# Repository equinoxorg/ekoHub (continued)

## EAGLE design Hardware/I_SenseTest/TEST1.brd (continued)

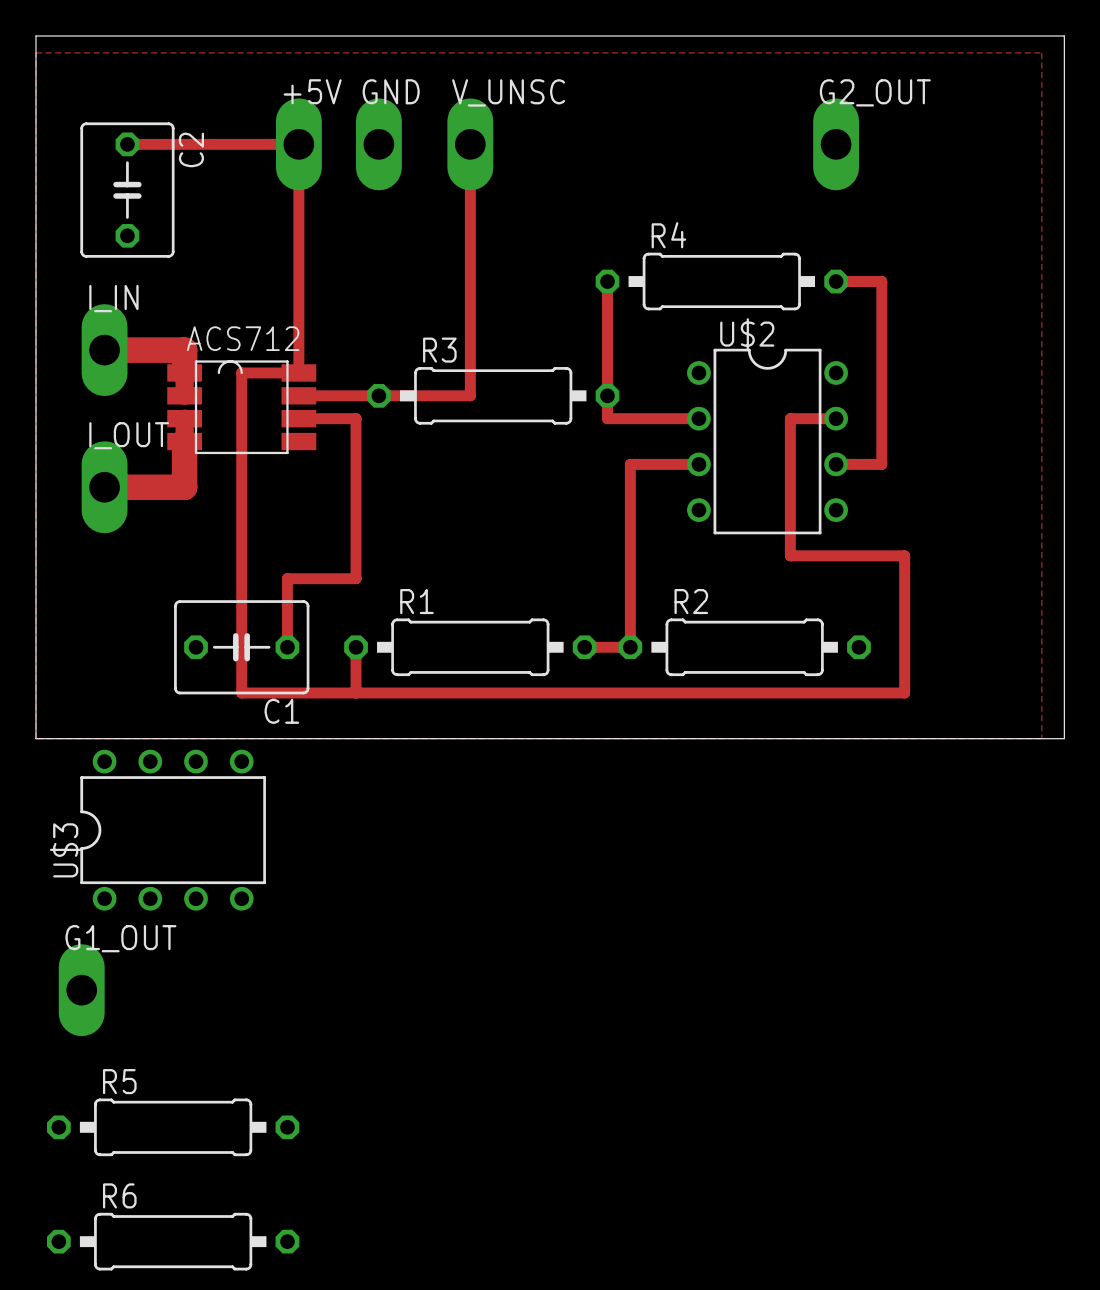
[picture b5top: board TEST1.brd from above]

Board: 2 copper layers, 57.1 x 39.0 mm, 18 parts (0 on the bottom side), 11 nets.

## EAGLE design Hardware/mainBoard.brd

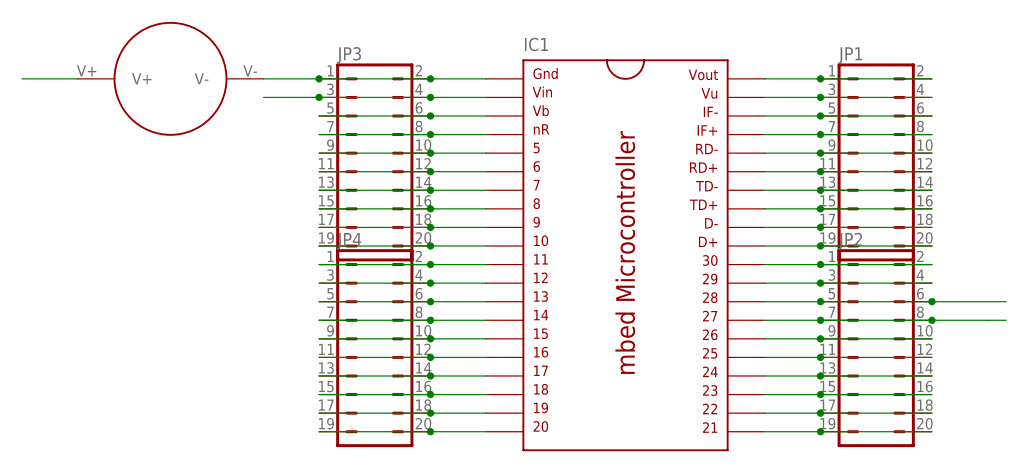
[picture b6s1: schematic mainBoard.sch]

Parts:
IC1: MBED_MICROCONTROLLER; DIL40_0.9
JP1, JP2, JP3, JP4: JP10Q
U$1: PANASONIC_BATTERYTHROUGH_HOLE; PANASONIC_BATTERY

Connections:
unnamed: IC1.1, JP3.1, JP3.2, U$1.V-
unnamed: IC1.40, JP1.1, JP1.2
unnamed: IC1.39, JP1.3, JP1.4
unnamed: IC1.38, JP1.5, JP1.6
unnamed: IC1.37, JP1.7, JP1.8
unnamed: IC1.36, JP1.9, JP1.10
unnamed: IC1.35, JP1.11, JP1.12
unnamed: IC1.34, JP1.13, JP1.14
unnamed: IC1.33, JP1.15, JP1.16
unnamed: IC1.32, JP1.17, JP1.18
unnamed: IC1.31, JP1.19, JP1.20
unnamed: IC1.30, JP2.1, JP2.2
unnamed: IC1.29, JP2.3, JP2.4
unnamed: IC1.26, JP2.9, JP2.10
unnamed: IC1.25, JP2.11, JP2.12
unnamed: IC1.24, JP2.13, JP2.14
unnamed: IC1.23, JP2.15, JP2.16
unnamed: IC1.22, JP2.17, JP2.18
unnamed: IC1.21, JP2.19, JP2.20
unnamed: IC1.4, JP3.7, JP3.8
unnamed: IC1.5, JP3.9, JP3.10
unnamed: IC1.6, JP3.11, JP3.12
unnamed: IC1.7, JP3.13, JP3.14
unnamed: IC1.8, JP3.15, JP3.16
unnamed: IC1.9, JP3.17, JP3.18
unnamed: IC1.10, JP3.19, JP3.20
unnamed: IC1.11, JP4.1, JP4.2
unnamed: IC1.12, JP4.3, JP4.4
unnamed: IC1.13, JP4.5, JP4.6
unnamed: IC1.14, JP4.7, JP4.8
unnamed: IC1.15, JP4.9, JP4.10
unnamed: IC1.16, JP4.11, JP4.12
unnamed: IC1.17, JP4.13, JP4.14
unnamed: IC1.18, JP4.15, JP4.16
unnamed: IC1.19, JP4.17, JP4.18
unnamed: IC1.20, JP4.19, JP4.20
SCL: IC1.27, JP2.7, JP2.8
SDA: IC1.28, JP2.5, JP2.6
VB: IC1.3, JP3.5, JP3.6, U$1.V+
VIN: IC1.2, JP3.3, JP3.4

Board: 2 copper layers, 6 parts (0 on the bottom side), 40 nets, no tracks yet.

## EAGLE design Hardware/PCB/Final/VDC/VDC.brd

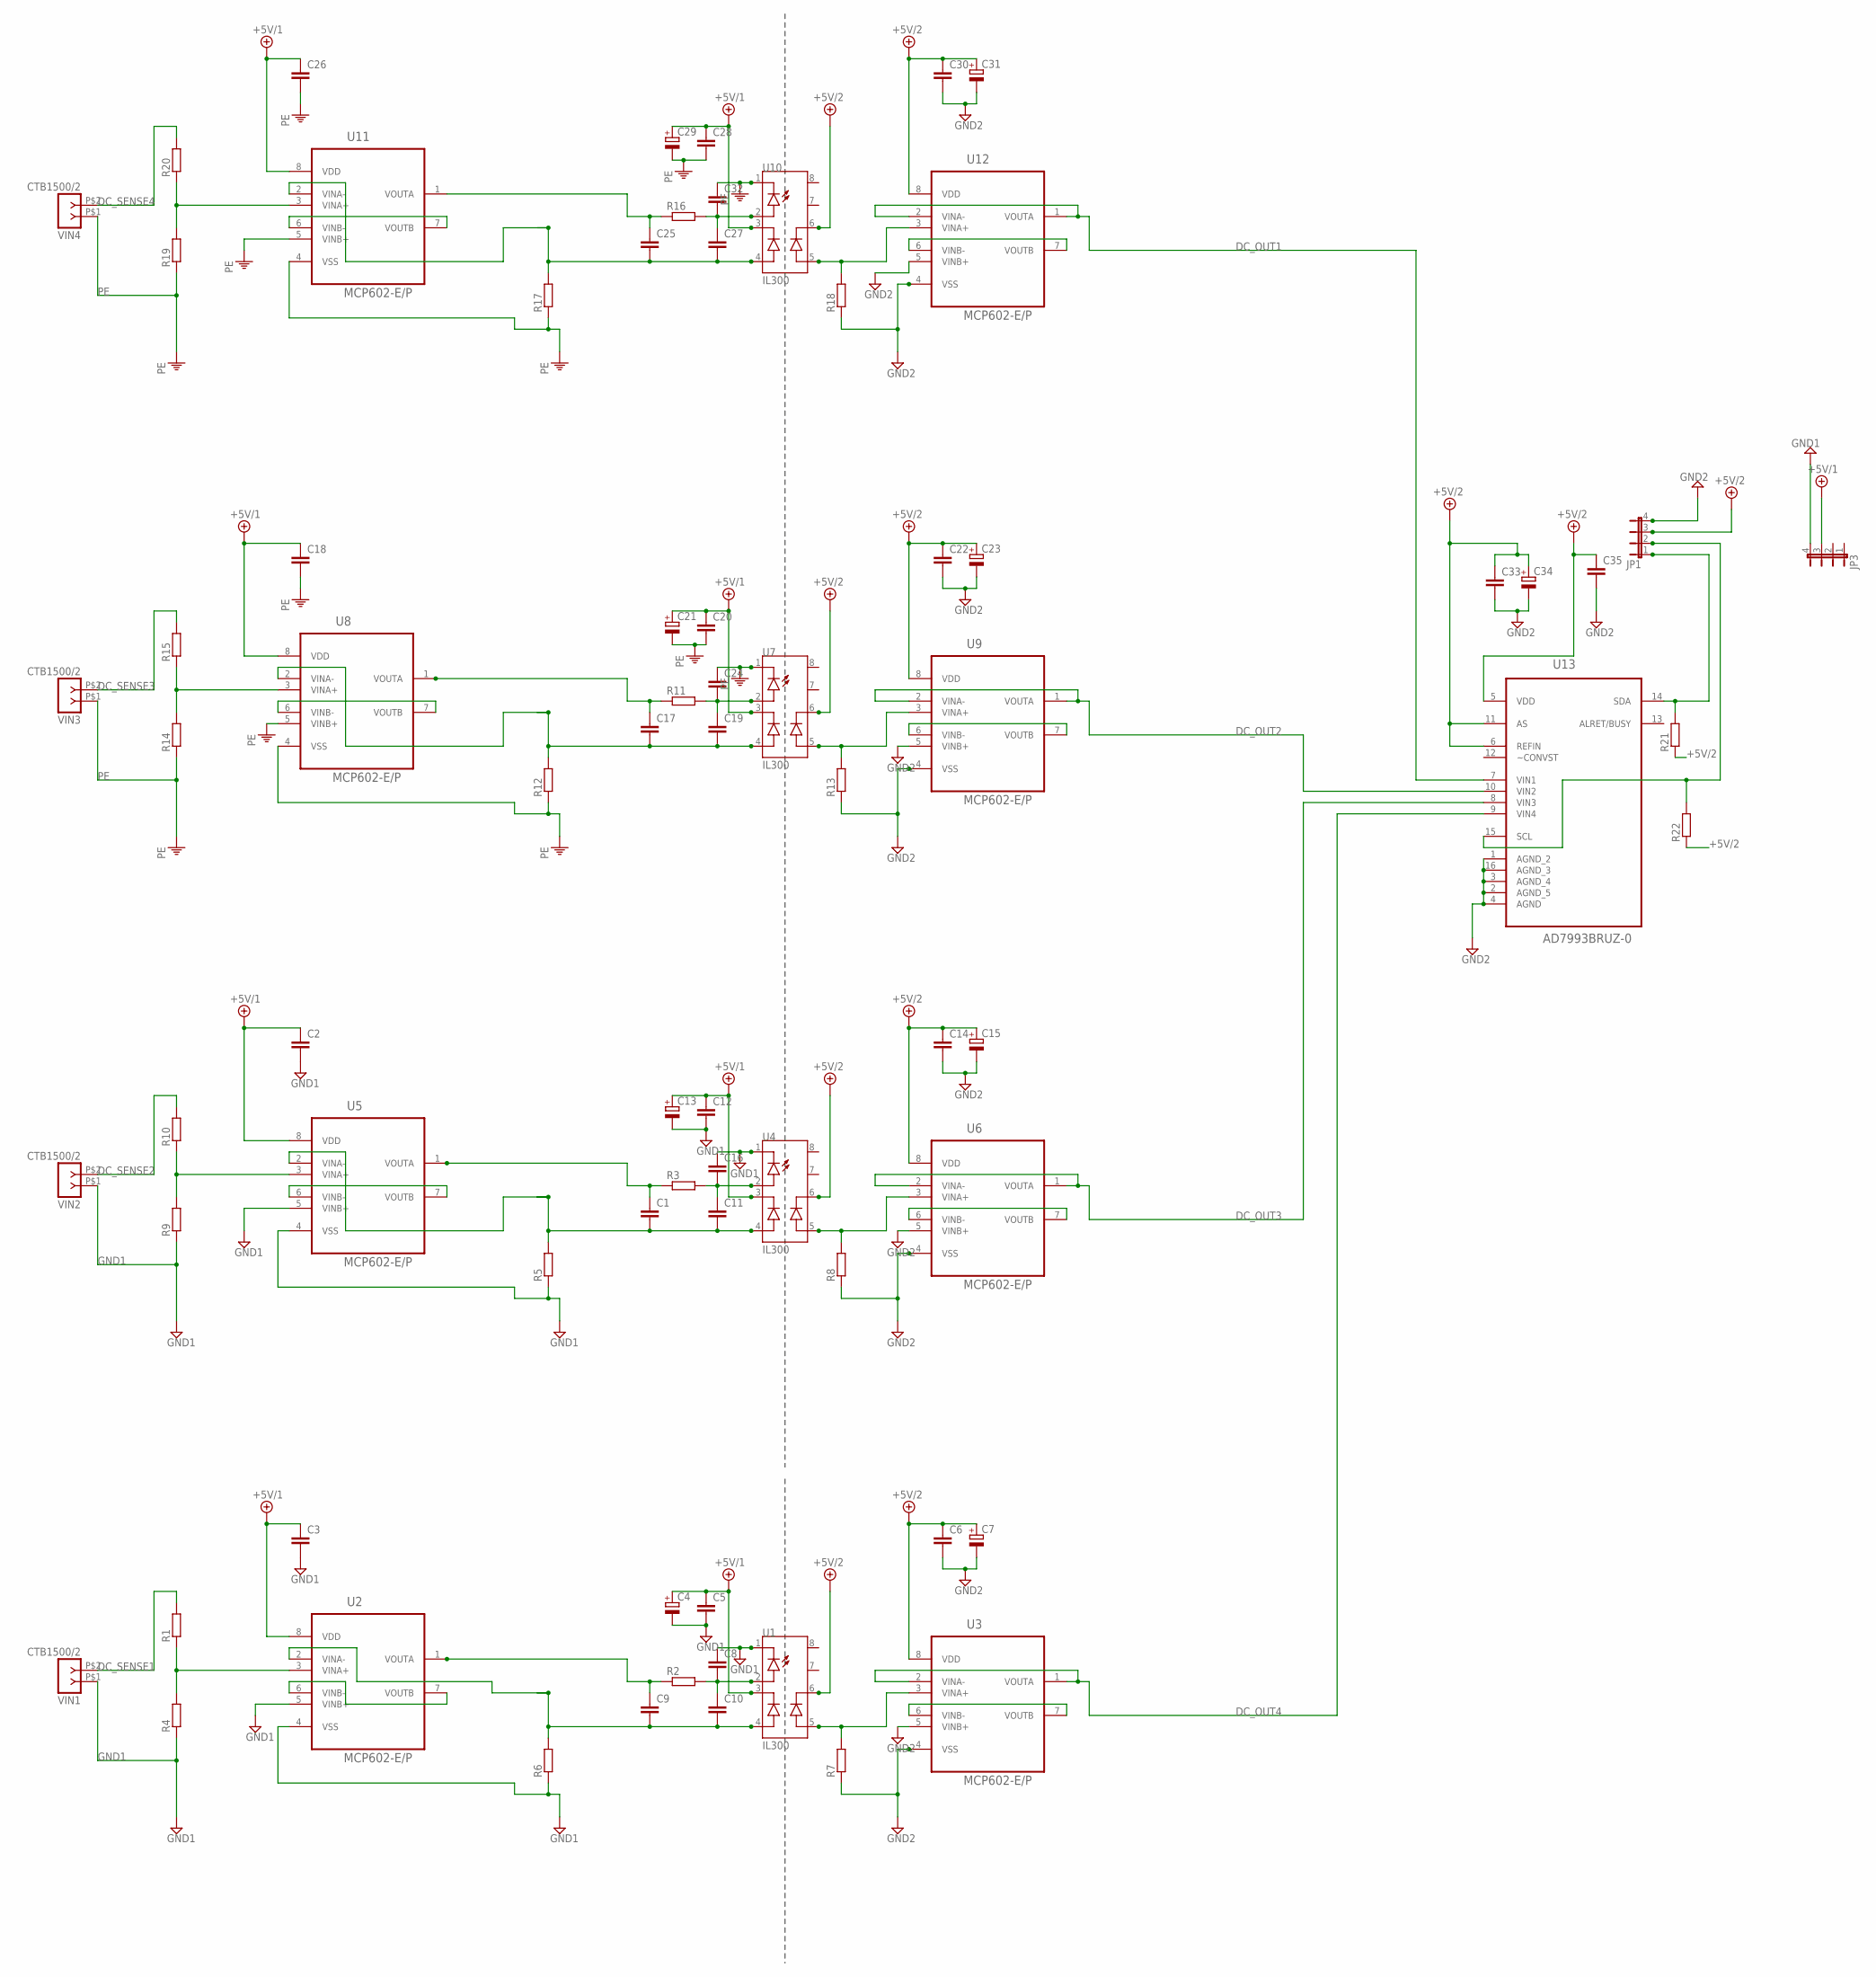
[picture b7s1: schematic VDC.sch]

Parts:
C1, C2, C3, C5, C6, C8, C9, C10, C11, C12, C14, C16, C17, C18, C19, C20, C22, C24, C25, C26, C27, C28, C30, C32: C-EU025-040X050; C025-040X050
C4, C7, C13, C15, C21, C23, C29, C31: CPOL-EUE2-5; E2-5
C33: C-EU025-024X044; C025-024X044
C34: CPOL-EUE2-4; E2-4
C35: C-EU025-025X050; C025-025X050
JP1, JP3: JP4E; JP4
R1, R2, R3, R4, R5, R6, R7, R8, R9, R10, R11, R12, R13, R14, R15, R16, R17, R18, R19, R20, R21, R22: R-EU_0207/10; 0207/10
U1, U4, U7, U10: IL300; DIL08
U2, U3, U5, U6, U8, U9, U11, U12: MCP602-E/P; DIP254P762X508-8P
U13: AD7993BRUZ-0; SOP65P640X120-16N
VIN1, VIN2, VIN3, VIN4: CTB1500/2; CTB1500-2

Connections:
+5V/1: C2.1, C3.1, C4.+, C5.1, C12.1, C13.+, C18.1, C20.1, C21.+, C26.1, C28.1, C29.+, JP3.3, U1.3 (C_FB), U2.8 (VDD), U4.3 (C_FB), U5.8 (VDD), U7.3 (C_FB), U8.8 (VDD), U10.3 (C_FB), U11.8 (VDD)
+5V/2: C6.1, C7.+, C14.1, C15.+, C22.1, C23.+, C30.1, C31.+, C33.1, C34.+, C35.1, JP1.3, R21.1, R22.1, U1.6 (C_OUT), U3.8 (VDD), U4.6 (C_OUT), U6.8 (VDD), U7.6 (C_OUT), U9.8 (VDD), U10.6 (C_OUT), U12.8 (VDD), U13.5 (VDD), U13.6 (REFIN), U13.11 (AS)
DC_OUT1: U12.1 (VOUTA), U12.2 (VINA-), U13.7 (VIN1)
DC_OUT2: U9.1 (VOUTA), U9.2 (VINA-), U13.10 (VIN2)
DC_OUT3: U6.1 (VOUTA), U6.2 (VINA-), U13.8 (VIN3)
DC_OUT4: U3.1 (VOUTA), U3.2 (VINA-), U13.9 (VIN4)
DC_SENSE1: R1.2, VIN1.P$2 (2)
DC_SENSE2: R10.2, VIN2.P$2 (2)
DC_SENSE3: R15.2, VIN3.P$2 (2)
DC_SENSE4: R20.2, VIN4.P$2 (2)
GND1: C2.2, C3.2, C4.-, C5.2, C8.1, C12.2, C13.-, C16.1, JP3.4, R4.1, R5.1, R6.1, R9.1, U1.1 (C_LED), U2.4 (VSS), U2.5 (VINB+), U4.1 (C_LED), U5.4 (VSS), U5.5 (VINB+), VIN1.P$1 (1), VIN2.P$1 (1)
GND2: C6.2, C7.-, C14.2, C15.-, C22.2, C23.-, C30.2, C31.-, C33.2, C34.-, C35.2, JP1.4, R7.1, R8.1, R13.1, R18.1, U3.4 (VSS), U3.5 (VINB+), U6.4 (VSS), U6.5 (VINB+), U9.4 (VSS), U9.5 (VINB+), U12.4 (VSS), U12.5 (VINB+), U13.1 (AGND_2), U13.2 (AGND_5), U13.3 (AGND_4), U13.4 (AGND), U13.16 (AGND_3)
unnamed: C9.2, C10.2, R6.2, U1.4 (A_FB), U2.2 (VINA-)
unnamed: C1.2, C11.2, R5.2, U4.4 (A_FB), U5.2 (VINA-)
unnamed: R7.2, U1.5 (A_OUT), U3.3 (VINA+)
unnamed: C8.2, C10.1, R2.2, U1.2 (A_LED)
unnamed: C9.1, R2.1, U2.1 (VOUTA)
unnamed: C11.1, C16.2, R3.2, U4.2 (A_LED)
unnamed: C1.1, R3.1, U5.1 (VOUTA)
unnamed: R1.1, R4.2, U2.3 (VINA+)
unnamed: R8.2, U4.5 (A_OUT), U6.3 (VINA+)
unnamed: R9.2, R10.1, U5.3 (VINA+)
unnamed: C17.2, C19.2, R12.2, U7.4 (A_FB), U8.2 (VINA-)
unnamed: C19.1, C24.2, R11.2, U7.2 (A_LED)
unnamed: C17.1, R11.1, U8.1 (VOUTA)
unnamed: R13.2, U7.5 (A_OUT), U9.3 (VINA+)
unnamed: R14.2, R15.1, U8.3 (VINA+)
unnamed: C25.2, C27.2, R17.2, U10.4 (A_FB), U11.2 (VINA-)
unnamed: C27.1, C32.2, R16.2, U10.2 (A_LED)
unnamed: C25.1, R16.1, U11.1 (VOUTA)
unnamed: R18.2, U10.5 (A_OUT), U12.3 (VINA+)
unnamed: R19.2, R20.1, U11.3 (VINA+)
unnamed: JP1.1, R21.2, U13.14 (SDA)
unnamed: JP1.2, R22.2, U13.15 (SCL)
unnamed: U11.6 (VINB-), U11.7 (VOUTB)
unnamed: U12.6 (VINB-), U12.7 (VOUTB)
unnamed: U8.6 (VINB-), U8.7 (VOUTB)
unnamed: U9.6 (VINB-), U9.7 (VOUTB)
unnamed: U5.6 (VINB-), U5.7 (VOUTB)
unnamed: U6.6 (VINB-), U6.7 (VOUTB)
unnamed: U2.6 (VINB-), U2.7 (VOUTB)
unnamed: U3.6 (VINB-), U3.7 (VOUTB)
PE: C18.2, C20.2, C21.-, C24.1, C26.2, C28.2, C29.-, C32.1, R12.1, R14.1, R17.1, R19.1, U7.1 (C_LED), U8.4 (VSS), U8.5 (VINB+), U10.1 (C_LED), U11.4 (VSS), U11.5 (VINB+), VIN3.P$1 (1), VIN4.P$1 (1)

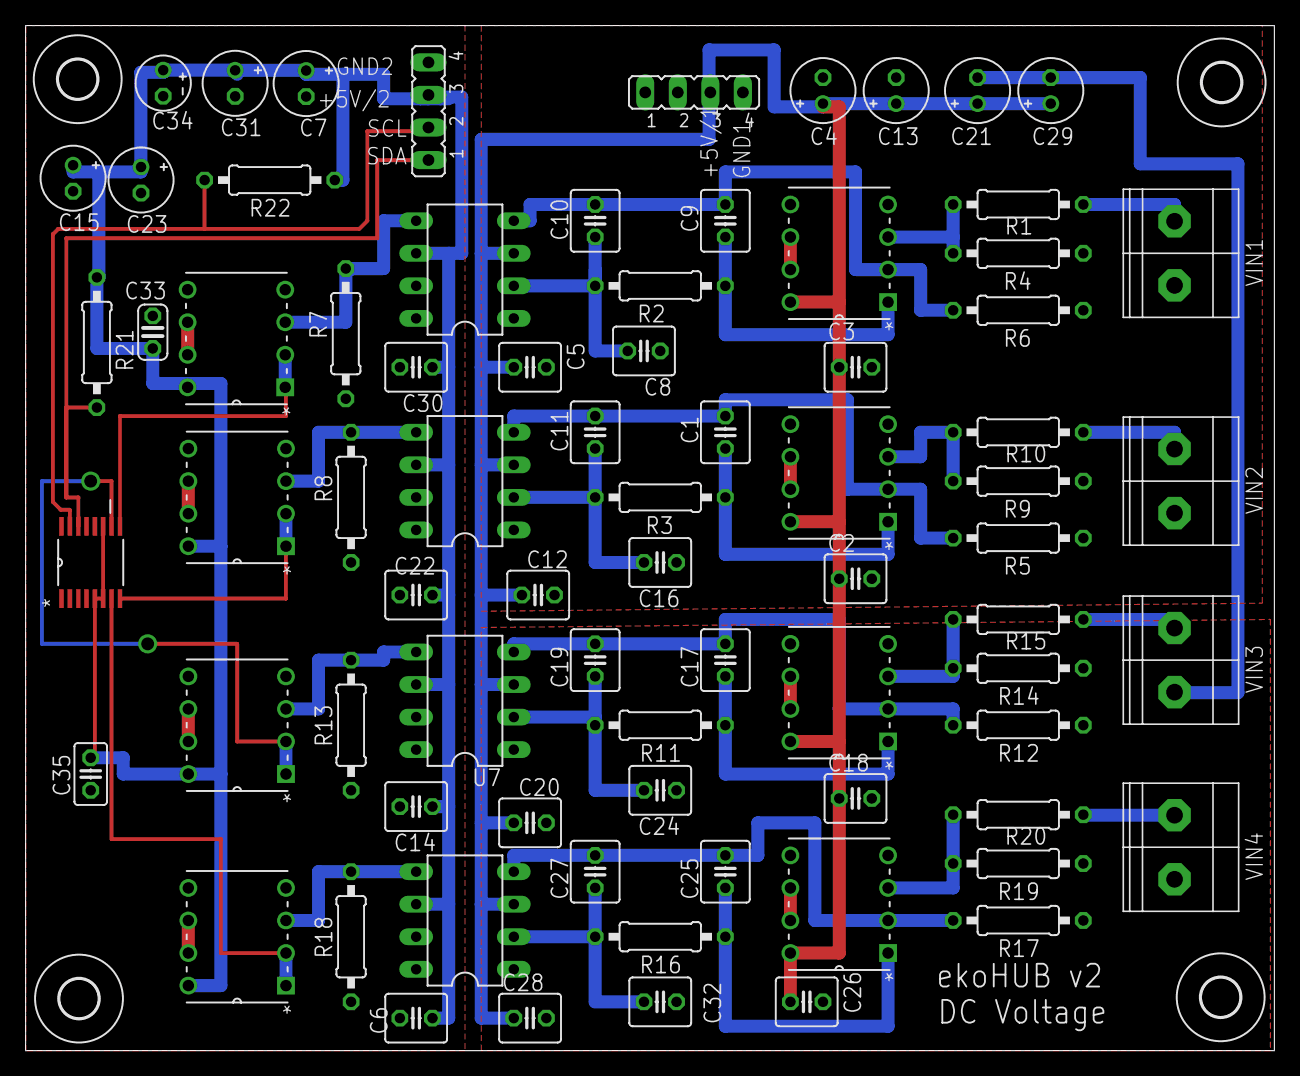
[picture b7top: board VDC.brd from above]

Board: 2 copper layers, 97.5 x 80.0 mm, 80 parts (0 on the bottom side), 43 nets.

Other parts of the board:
U$1, U$2, U$3, U$4: 3,0

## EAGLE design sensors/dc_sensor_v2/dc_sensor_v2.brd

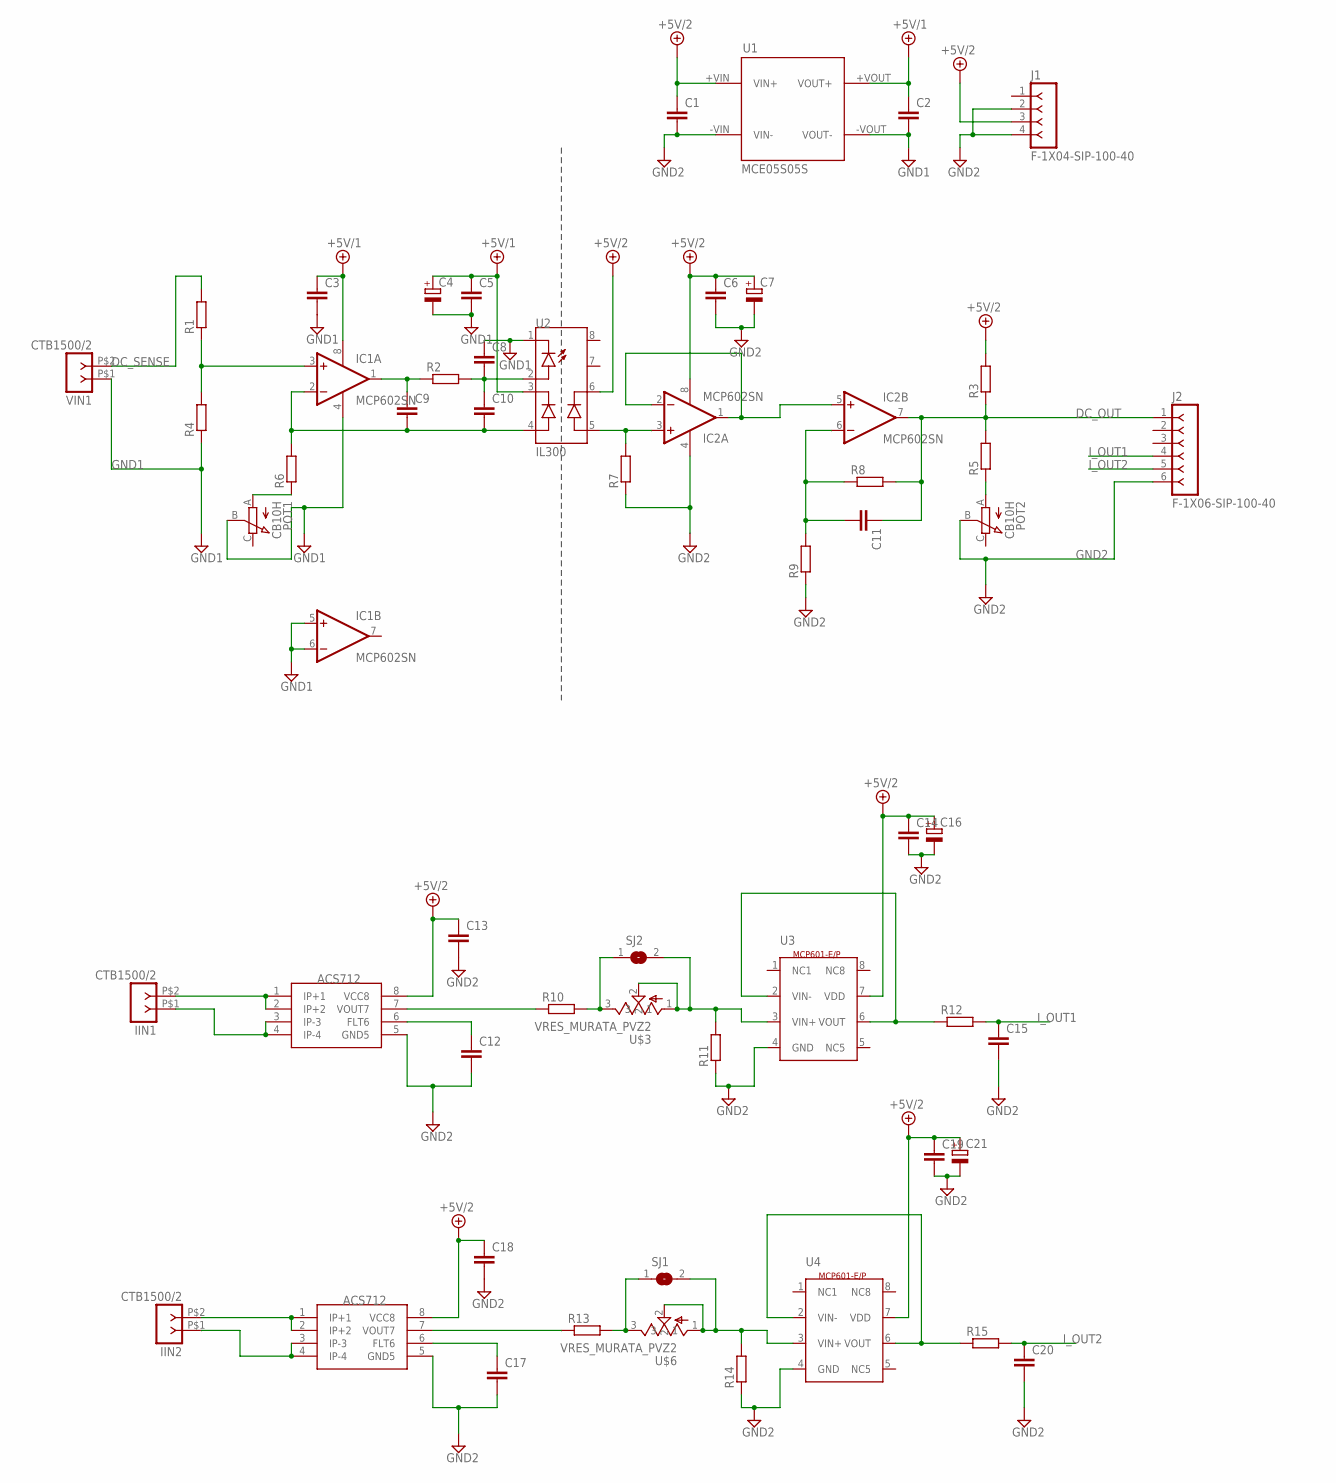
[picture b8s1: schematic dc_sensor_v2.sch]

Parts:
C1, C2: C-EUC1206; C1206
C3, C5, C6, C8, C9, C10, C11: C-EU025-040X050; C025-040X050
C4, C7: CPOL-EUE2-5; E2-5
C12, C15, C17, C20: C-EU025-030X050; C025-030X050
C13, C14, C18, C19: C-EUC0603; C0603
C16, C21: CPOL-EUE2.5-6; E2,5-6
IC1, IC2: MCP602SN; SO08
IIN1, IIN2: CTB1500/2; CTB1500-2
J1: F-1X04-SIP-100-40; SIP-100-04-40
J2: F-1X06-SIP-100-40; SIP-100-06-40
POT1, POT2: CB10H; CB10V
R1, R2, R3, R4, R5, R6, R7, R8, R9, R10, R11, R12, R13, R14, R15: R-EU_0207/10; 0207/10
SJ1, SJ2: SJ
U1: MCE05S05S; MCEXXSXXS_SIP
U2: IL300; DIL08
U3, U4: MCP601; SO8
U5, U6: ACS712; SO8
U$3, U$6: VRES_MURATA_PVZ2; MURATA_PVZ2A
VIN1: CTB1500/2; CTB1500-2

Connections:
+5V/1: C2.1, C3.1, C4.+, C5.1, IC1.8 (V+), U1.+VOUT (VOUT+), U2.3 (C_FB)
+5V/2: C1.1, C6.1, C7.+, C13.1, C14.1, C16.+, C18.1, C19.1, C21.+, IC2.8 (V+), J1.3, R3.2, U1.+VIN (VIN+), U2.6 (C_OUT), U3.7 (VDD), U4.7 (VDD), U5.8 (VCC8), U6.8 (VCC8)
DC_OUT: C11.1, IC2.7 (OUT), J2.1, R3.1, R5.2, R8.2
DC_SENSE: R1.2, VIN1.P$2 (2)
GND1: C2.2, C3.2, C4.-, C5.2, C8.1, IC1.4 (V-), IC1.5 (+IN), IC1.6 (-IN), POT1.B (S), R4.1, U1.-VOUT (VOUT-), U2.1 (C_LED), VIN1.P$1 (1)
GND2: C1.2, C6.2, C7.-, C12.2, C13.2, C14.2, C15.2, C16.-, C17.2, C18.2, C19.2, C20.2, C21.-, IC2.4 (V-), J1.2, J1.4, J2.6, POT2.B (S), R7.1, R9.1, R11.1, R14.1, U1.-VIN (VIN-), U3.4 (GND), U4.4 (GND), U5.5 (GND5), U6.5 (GND5)
I_OUT1: C15.1, J2.4, R12.2
I_OUT2: C20.1, J2.5, R15.2
unnamed: C9.2, C10.2, IC1.2 (-IN), R6.2, U2.4 (A_FB)
unnamed: POT2.A, R5.1
unnamed: IC2.3 (+IN), R7.2, U2.5 (A_OUT)
unnamed: C8.2, C10.1, R2.2, U2.2 (A_LED)
unnamed: C9.1, IC1.1 (OUT), R2.1
unnamed: IC2.1 (OUT), IC2.2 (-IN), IC2.5 (+IN)
unnamed: POT1.A, R6.1
unnamed: IC1.3 (+IN), R1.1, R4.2
unnamed: IIN1.P$2 (2), U6.1 (IP+1), U6.2 (IP+2)
unnamed: C11.2, IC2.6 (-IN), R8.1, R9.2
unnamed: IIN1.P$1 (1), U6.3 (IP-3), U6.4 (IP-4)
unnamed: R10.2, SJ2.1, U$3.3
unnamed: C12.1, U6.6 (FLT6)
unnamed: R12.1, U3.2 (VIN-), U3.6 (VOUT)
unnamed: IIN2.P$2 (2), U5.1 (IP+1), U5.2 (IP+2)
unnamed: R10.1, U6.7 (VOUT7)
unnamed: R11.2, SJ2.2, U3.3 (VIN+), U$3.1, U$3.2
unnamed: IIN2.P$1 (1), U5.3 (IP-3), U5.4 (IP-4)
unnamed: C17.1, U5.6 (FLT6)
unnamed: R13.1, U5.7 (VOUT7)
unnamed: R14.2, SJ1.2, U4.3 (VIN+), U$6.1, U$6.2
unnamed: R13.2, SJ1.1, U$6.3
unnamed: R15.1, U4.2 (VIN-), U4.6 (VOUT)

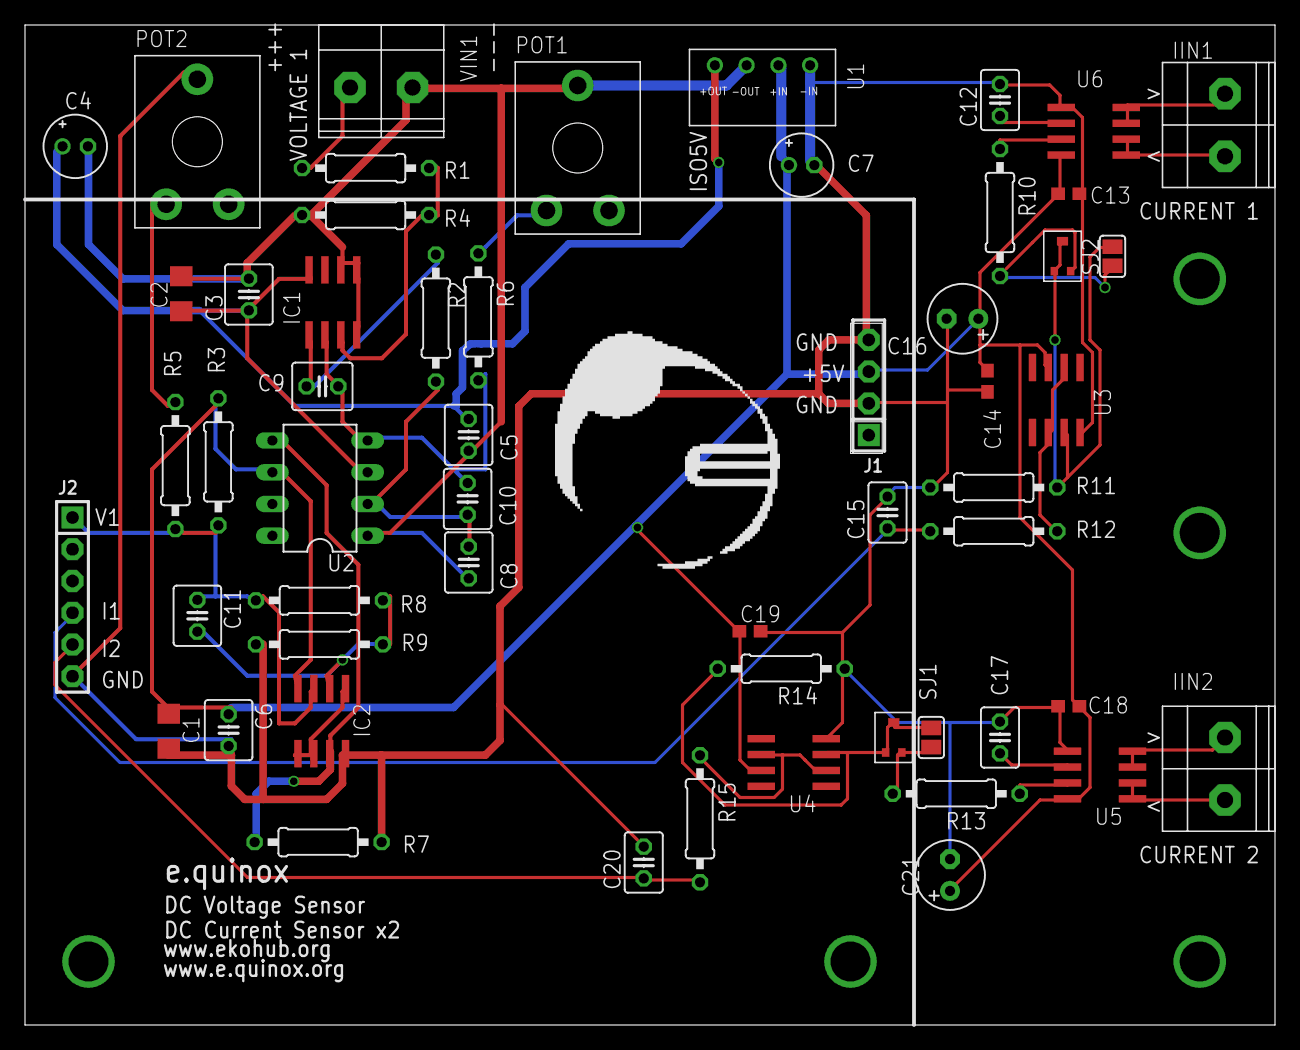
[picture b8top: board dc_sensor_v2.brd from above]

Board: 2 copper layers, 100.0 x 80.0 mm, 56 parts (0 on the bottom side), 31 nets.

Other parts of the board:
U$1: EQNXLOGO

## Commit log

2011-09-18 Initial commit of eko_upload
2011-09-19 Added JSON RPC and CURD interfaces for Messages and Heartbeat
2011-09-19 FileUpload handler added with test code.\nTweaks added to make it play nice with python 2.5 on GAE servers
2011-09-19 Added FileUpoad handler for uploads to blobstore. Fixes for date-time JSON serialisation in Python2.5. Minor cosmetic changes to CSS stylesheets.
2011-09-19 Updated RPCHandlers to make use of memcache when fetching kiosk object and public keys. Removed per function instantiation of BaseConverter(). Added Kiosk Message RPC through function post_message().
2011-09-20 Changes to cache behaviour and templates.
    More handlers now cache data in memcache.
    Data Tables use JQuery ThemeRoller.
    Improvements to layout.
2011-09-25 Minor fixes.
2011-09-25 Fix omission of kiosk id to sync session records.
2011-10-10 Major refactoring. Production Ready.
2011-11-07 Merged some presentation code from legacy project.
2012-02-08 Added cosmetic improvements.
2012-07-23 clean up folder structure
2012-07-23 clean up folder structure 2
    * Removed gerber files, PDFs and other outdated material
    * Reorganised LBR files to library folder
    * Organised board designs into three main categories
2012-07-24 Added FTDI based isolated RS485 test device
    * New footprint for Pheonix Contact PTSM 4-way socket
    * Footrpints for MOLEX 47346-0001, TE1981584-1 and MC32594 USB sockets
    (Micro B, Micro AB and Stacked A respectively).
    * New schematic for FT232R based RS485 adaptor utilising HCPL2630-series
    opto-isolators.
    * Utilised Cliff Electronics 2.1mm SMT DC jack connector from
2012-07-24 Created ftdi_modbus_v2 layout
2012-07-25 Added DC Sensor v2 with updated libraries
2012-08-05 Completed layout of ftdi_rs485_v2 test board. Added more status LEDs
2012-08-07 Created base for ekobb_r4 update.
2012-08-07 Added xbee adaptor schematic from Dropbox folder.§
2012-08-11 Added new PicKit 3 Apdapter board design
2012-08-11 Line Termination Board - Initial Layout
2012-08-15 Created initial schematic and layout for 5-level immersion water sensors.
    Basic theory of operation:
    1) mbed generates square wave at 1kHz frequency
    2) MCP602 opamp configured as schmitt trigger generates 10Vpp AC signal
    3) Terminal Connector 6 connected to deepest electrode
    4) On contact, other electrodes form conductive path for AC signal
    5) Opamp buffers source/sink current
2012-08-16 Completed layout of water level sensor.
    TODO:
    Check circuit
    Add status LEDs
    Add bias resistors to GND
2012-08-16 Added LEDs and Bias Resistors to water sensor
2012-08-16 Completed water level sensor / wireless network board.
    Added status LEDs
    Added test points for critical signals
    Added M3 mounting holes
2012-08-16 [WSensor] Fixed bug with unconnected opamp input. Fixed component values.
2012-08-16 Minor modifications to PicKit 3 adaptor
2012-08-16 Updated DC voltage sensor to rev 2
2012-08-16 Resized pickit adaptor to fit into 5x5 pcb
2012-08-16 Misc DRC fixes
2012-08-17 Updated with fusion order number
2012-08-18 Added DesignSpark libraries
2012-08-31 Modified code to be more configurable at boot via command line.
    Adopted to utilise PyCrypto 2.3+, RSA.importKey()
    Modified to use context dict passed from main.py
    Stripped all hardware dependant code for later incorporation with board_config hooks.
2012-08-31 Updated sensor dispatch code to accept global context dict. Unittests added for web sync code.
2012-08-31 Added README with project info and reorganised tools directory.
2012-08-31 minor additions to readme
2012-08-31 Fixed failure with upload_file()
2012-08-31 Fixed issue with renamed log files and bitrot in configtool.py
2012-09-01 Added new configuration tool for R2/R3 network boards
2012-09-01 Added README.md. Fixed typo in main.c.
2012-09-01 Added cmd prompt script
2012-09-02 Updated pppd_scriptgen.py
2012-09-02 Documentation fix for pppdscriptgen
2012-09-06 Updated setup scripts, configtool and pppd_scriptgen
2012-09-07 Updated default config file sample
2012-09-07 Cleaned up command line parameters
2013-09-21 First Commit
    All Files on the datalogging dropbox uploaded to GIthub
2013-09-30 Added summer trip learning experiences document
    Document which describes the improvements that should be made from the
    lessons learnt from the summer expedition.
2013-10-18 Removed a conflicting file
2013-10-18 Reorganized the entire Folder
2013-10-18 Made changes to the PCB Folders
2014-01-05 Sensor Testing and PCB Designs
    Added sensor testing data and PCB designs for AC voltage and Current
    sensor
2014-01-20 First Draft of Main Board
    1. Added most of the main board parts in the schematic.
    2. Board layout needs work. the backlight timing circuit needs to be
    tested.
    3. Part sizes need to be double checked.
    4. Need to add molex connectors for Input, I2C Bus, and Power Bus
    5. Double check decoupling capacitors
2014-01-20 Edited the ReadMe File
2014-01-27 Main Board Work in Progress
    Work in Progress on the main board.
    Need to test the timing circuit and then finalize and finish routing the
    board.
2014-01-30 Added Component Values for the AC Voltage sensor
2014-02-01 Updated the Main Board
    Main Board is Fully Done. need to Test the timing circuit before sending
    the design for manufacture
2014-02-02 Main Board Ready for In-House Manufacture
2014-02-05 Added Gerber Files for Main Board
2014-03-01 Changed the TRACO Part and USB clearance fix
2014-04-22 Changed mounting holes and SD card Power pin
    1. The mounting holes locations have been changed slightly so that they
    are to the nearest mm
    2. The SD card can be power gated using pin 9.
2014-04-22 Added power control of the LCD screen
2014-04-24 Added Reverse Polarity Protection
2014-04-26 Board Layouts done for DC Current and AC Board
2014-05-05 Added box model
2014-05-05 DC Voltage Sensor board added
2014-05-08 First components order by David
2014-05-10 DC Current Board - Done by Saurab
2014-05-21 v1.0, AC sinewave algorithm
2014-05-21 Final Version: RMS voltage calculation working
2014-05-25 merged web app
2014-05-25 updated finance sheet
2014-05-28 website remote settings addition
2014-06-09 Added graph selection panel and login button
2014-06-10 implemented user service, login/logout button work perfectly
2014-06-10 graph parameter update working fine
2014-06-10 application performs a query for each dataset to display
2014-07-05 trying add dropdown feature on "kiosk" tab
2014-07-06 changed to bootstrap version 3. Implemented drop down menu
2014-07-12 improved layout structure. Terrible rendering when resizing window
2014-07-17 implemented download form. Tried to test jQuery. didn't work
2014-07-17 can almost display range of dates on the download form. Have to implement code for download link
2014-07-20 can query start and end dates and display them in correct format on the webpage.
2014-07-22 can retrieve data based on selected date range
2014-07-24 Download works. created a hidden input in the form to pass the downloading flag as a query string.
2014-07-27 added download form validation code
2014-07-27 improved remote control interface
2014-08-02 deployed app for the first time. Tested json formatted remote data fetch from mbed. Works well
2014-09-14 implemented parser of json string received from the mbed and the values are saved to datastore
2014-09-14 using response object's out property to reply to client.
2014-09-18 Graphs are now being plotted against the actual timestamps of the sensor values not tdate.
2014-09-19 Changed the remote settings form. Added hour and minutes selectors for the time parameters. Data is saved correctly
2014-09-20 Settings for different kiosks can now be saved to the datastore
2014-09-20 now checking which Kiosk is requesting for remote settings in order to send the settings to the correct kiosk
2014-09-25 confirmation message is displayed when settings are saved
2015-01-21 now merged two repos
2015-02-18 created folder 14-15:
2015-02-18 moved arduino code to Software 14-15
2015-02-19 Tested i2c master/slave on two arduinos
2015-02-23 removed statistics table next to graph
2015-02-25 Latest upload
2015-02-25 Tried to connect to GSM with Gallo's SIM Card but PIN got blocked
2015-07-01 removed 'kiosks and 'About' tabs
